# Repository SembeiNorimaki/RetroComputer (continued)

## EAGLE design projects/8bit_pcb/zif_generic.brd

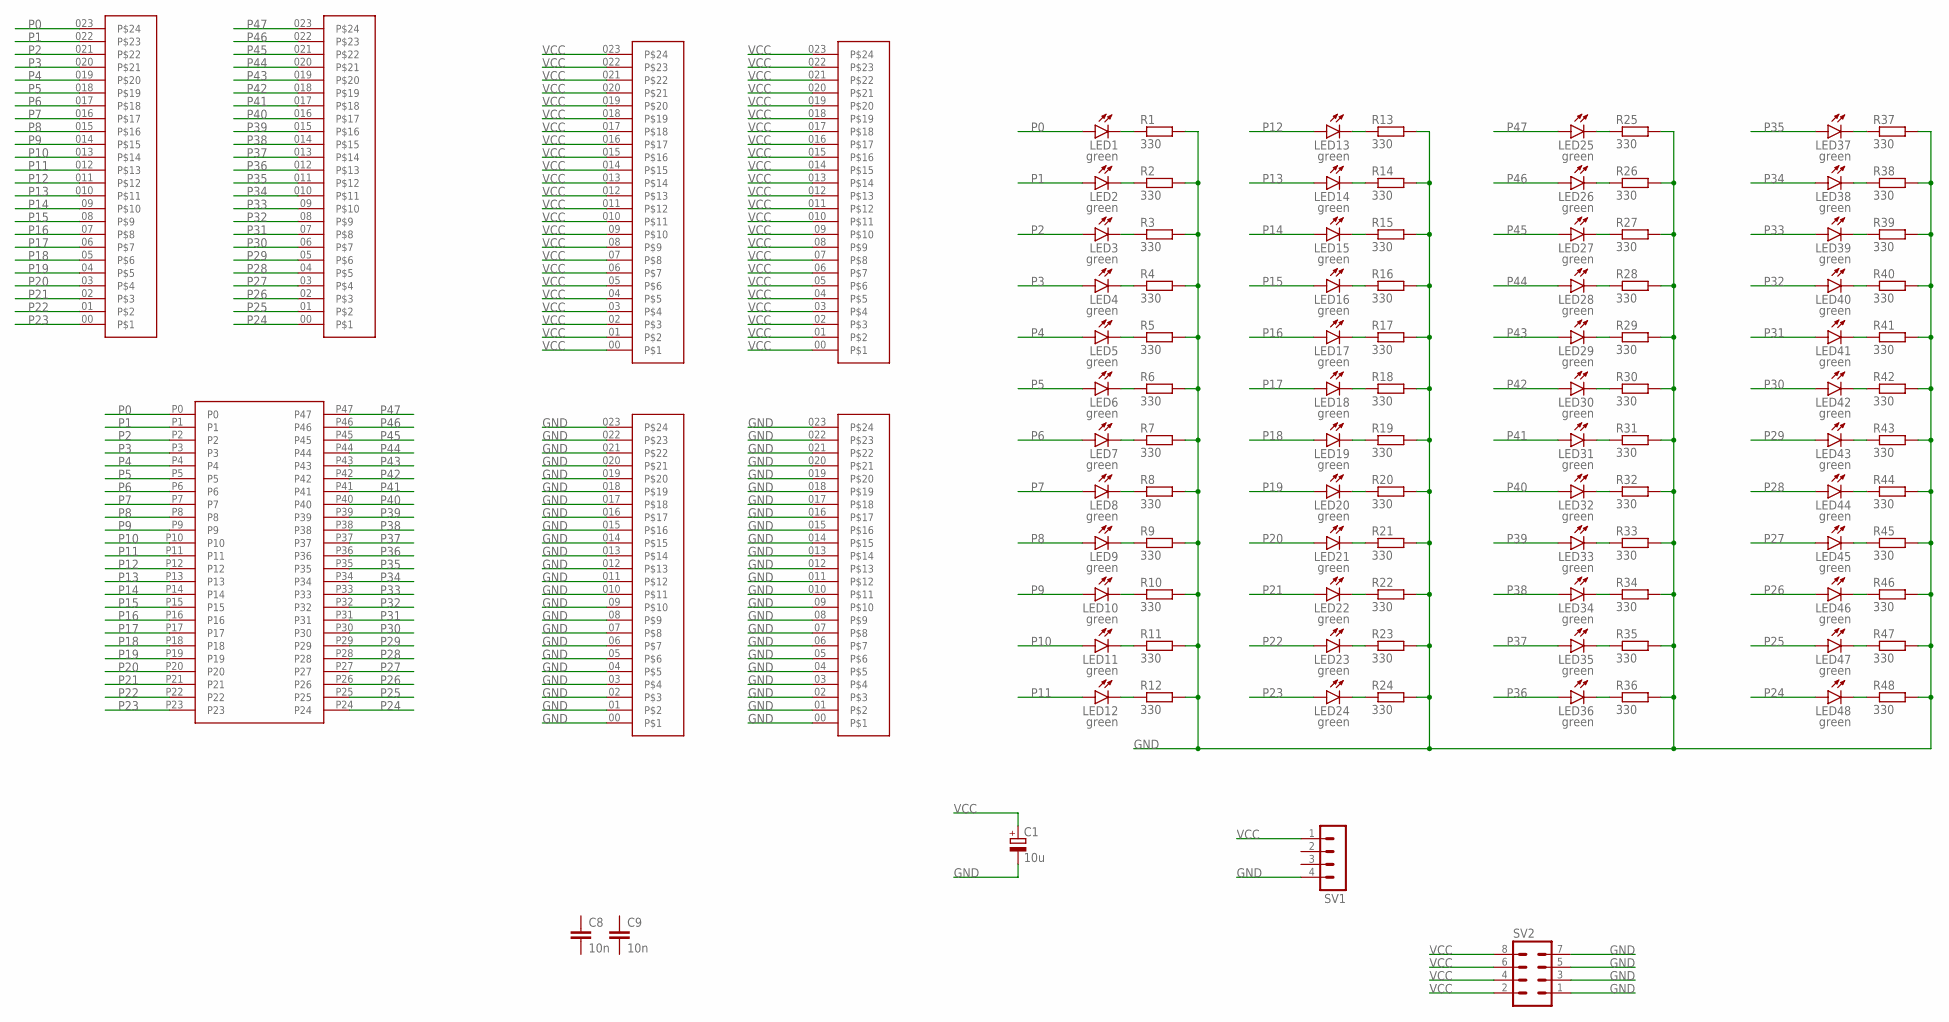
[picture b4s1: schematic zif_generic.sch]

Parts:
C1: 10u; E5-8,5
C8, C9: 10n; C050-025X075
LED1, LED2, LED3, LED4, LED5, LED6, LED7, LED8, LED9, LED10, LED11, LED12, LED13, LED14, LED15, LED16, LED17, LED18, LED19, LED20, LED21, LED22, LED23, LED24, LED25, LED26, LED27, LED28, LED29, LED30, LED31, LED32, LED33, LED34, LED35, LED36, LED37, LED38, LED39, LED40, LED41, LED42, LED43, LED44, LED45, LED46, LED47, LED48: green; SML1206
R1, R2, R3, R4, R5, R6, R7, R8, R9, R10, R11, R12, R13, R14, R15, R16, R17, R18, R19, R20, R21, R22, R23, R24, R25, R26, R27, R28, R29, R30, R31, R32, R33, R34, R35, R36, R37, R38, R39, R40, R41, R42, R43, R44, R45, R46, R47, R48: 330; R0805
SV1: MA04-1
SV2: MA04-2
U$1, U$2, U$3, U$4, U$5, U$6: PIN_1X24
U$7: ZIF_24X2

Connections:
GND: C1.-, R1.2, R2.2, R3.2, R4.2, R5.2, R6.2, R7.2, R8.2, R9.2, R10.2, R11.2, R12.2, R13.2, R14.2, R15.2, R16.2, R17.2, R18.2, R19.2, R20.2, R21.2, R22.2, R23.2, R24.2, R25.2, R26.2, R27.2, R28.2, R29.2, R30.2, R31.2, R32.2, R33.2, R34.2, R35.2, R36.2, R37.2, R38.2, R39.2, R40.2, R41.2, R42.2, R43.2, R44.2, R45.2, R46.2, R47.2, R48.2, SV1.4, SV2.1, SV2.3, SV2.5, SV2.7, U$2.00, U$2.01, U$2.02, U$2.03, U$2.04, U$2.05, U$2.06, U$2.07, U$2.08, U$2.09, U$2.010, U$2.011, U$2.012, U$2.013, U$2.014, U$2.015, U$2.016, U$2.017, U$2.018, U$2.019, U$2.020, U$2.021, U$2.022, U$2.023, U$5.00, U$5.01, U$5.02, U$5.03, U$5.04, U$5.05, U$5.06, U$5.07, U$5.08, U$5.09, U$5.010, U$5.011, U$5.012, U$5.013, U$5.014, U$5.015, U$5.016, U$5.017, U$5.018, U$5.019, U$5.020, U$5.021, U$5.022, U$5.023
unnamed: LED1.C, R1.1
unnamed: LED2.C, R2.1
unnamed: LED3.C, R3.1
unnamed: LED4.C, R4.1
unnamed: LED5.C, R5.1
unnamed: LED6.C, R6.1
unnamed: LED7.C, R7.1
unnamed: LED8.C, R8.1
unnamed: LED9.C, R9.1
unnamed: LED10.C, R10.1
unnamed: LED11.C, R11.1
unnamed: LED12.C, R12.1
unnamed: LED13.C, R13.1
unnamed: LED14.C, R14.1
unnamed: LED15.C, R15.1
unnamed: LED16.C, R16.1
unnamed: LED17.C, R17.1
unnamed: LED18.C, R18.1
unnamed: LED19.C, R19.1
unnamed: LED20.C, R20.1
unnamed: LED21.C, R21.1
unnamed: LED22.C, R22.1
unnamed: LED23.C, R23.1
unnamed: LED24.C, R24.1
unnamed: LED25.C, R25.1
unnamed: LED26.C, R26.1
unnamed: LED27.C, R27.1
unnamed: LED28.C, R28.1
unnamed: LED29.C, R29.1
unnamed: LED30.C, R30.1
unnamed: LED31.C, R31.1
unnamed: LED32.C, R32.1
unnamed: LED33.C, R33.1
unnamed: LED34.C, R34.1
unnamed: LED35.C, R35.1
unnamed: LED36.C, R36.1
unnamed: LED37.C, R37.1
unnamed: LED38.C, R38.1
unnamed: LED39.C, R39.1
unnamed: LED40.C, R40.1
unnamed: LED41.C, R41.1
unnamed: LED42.C, R42.1
unnamed: LED43.C, R43.1
unnamed: LED44.C, R44.1
unnamed: LED45.C, R45.1
unnamed: LED46.C, R46.1
unnamed: LED47.C, R47.1
unnamed: LED48.C, R48.1
P0: LED1.A, U$4.023, U$7.P0
P1: LED2.A, U$4.022, U$7.P1
P2: LED3.A, U$4.021, U$7.P2
P3: LED4.A, U$4.020, U$7.P3
P4: LED5.A, U$4.019, U$7.P4
P5: LED6.A, U$4.018, U$7.P5
P6: LED7.A, U$4.017, U$7.P6
P7: LED8.A, U$4.016, U$7.P7
P8: LED9.A, U$4.015, U$7.P8
P9: LED10.A, U$4.014, U$7.P9
P10: LED11.A, U$4.013, U$7.P10
P11: LED12.A, U$4.012, U$7.P11
P12: LED13.A, U$4.011, U$7.P12
P13: LED14.A, U$4.010, U$7.P13
P14: LED15.A, U$4.09, U$7.P14
P15: LED16.A, U$4.08, U$7.P15
P16: LED17.A, U$4.07, U$7.P16
P17: LED18.A, U$4.06, U$7.P17
P18: LED19.A, U$4.05, U$7.P18
P19: LED20.A, U$4.04, U$7.P19
P20: LED21.A, U$4.03, U$7.P20
P21: LED22.A, U$4.02, U$7.P21
P22: LED23.A, U$4.01, U$7.P22
P23: LED24.A, U$4.00, U$7.P23
P24: LED48.A, U$1.00, U$7.P24
P25: LED47.A, U$1.01, U$7.P25
P26: LED46.A, U$1.02, U$7.P26
P27: LED45.A, U$1.03, U$7.P27
P28: LED44.A, U$1.04, U$7.P28
P29: LED43.A, U$1.05, U$7.P29
P30: LED42.A, U$1.06, U$7.P30
P31: LED41.A, U$1.07, U$7.P31
P32: LED40.A, U$1.08, U$7.P32
P33: LED39.A, U$1.09, U$7.P33
P34: LED38.A, U$1.010, U$7.P34
P35: LED37.A, U$1.011, U$7.P35
P36: LED36.A, U$1.012, U$7.P36
P37: LED35.A, U$1.013, U$7.P37
P38: LED34.A, U$1.014, U$7.P38
P39: LED33.A, U$1.015, U$7.P39
P40: LED32.A, U$1.016, U$7.P40
P41: LED31.A, U$1.017, U$7.P41
P42: LED30.A, U$1.018, U$7.P42
P43: LED29.A, U$1.019, U$7.P43
P44: LED28.A, U$1.020, U$7.P44
P45: LED27.A, U$1.021, U$7.P45
P46: LED26.A, U$1.022, U$7.P46
P47: LED25.A, U$1.023, U$7.P47
VCC: C1.+, SV1.1, SV2.2, SV2.4, SV2.6, SV2.8, U$3.00, U$3.01, U$3.02, U$3.03, U$3.04, U$3.05, U$3.06, U$3.07, U$3.08, U$3.09, U$3.010, U$3.011, U$3.012, U$3.013, U$3.014, U$3.015, U$3.016, U$3.017, U$3.018, U$3.019, U$3.020, U$3.021, U$3.022, U$3.023, U$6.00, U$6.01, U$6.02, U$6.03, U$6.04, U$6.05, U$6.06, U$6.07, U$6.08, U$6.09, U$6.010, U$6.011, U$6.012, U$6.013, U$6.014, U$6.015, U$6.016, U$6.017, U$6.018, U$6.019, U$6.020, U$6.021, U$6.022, U$6.023

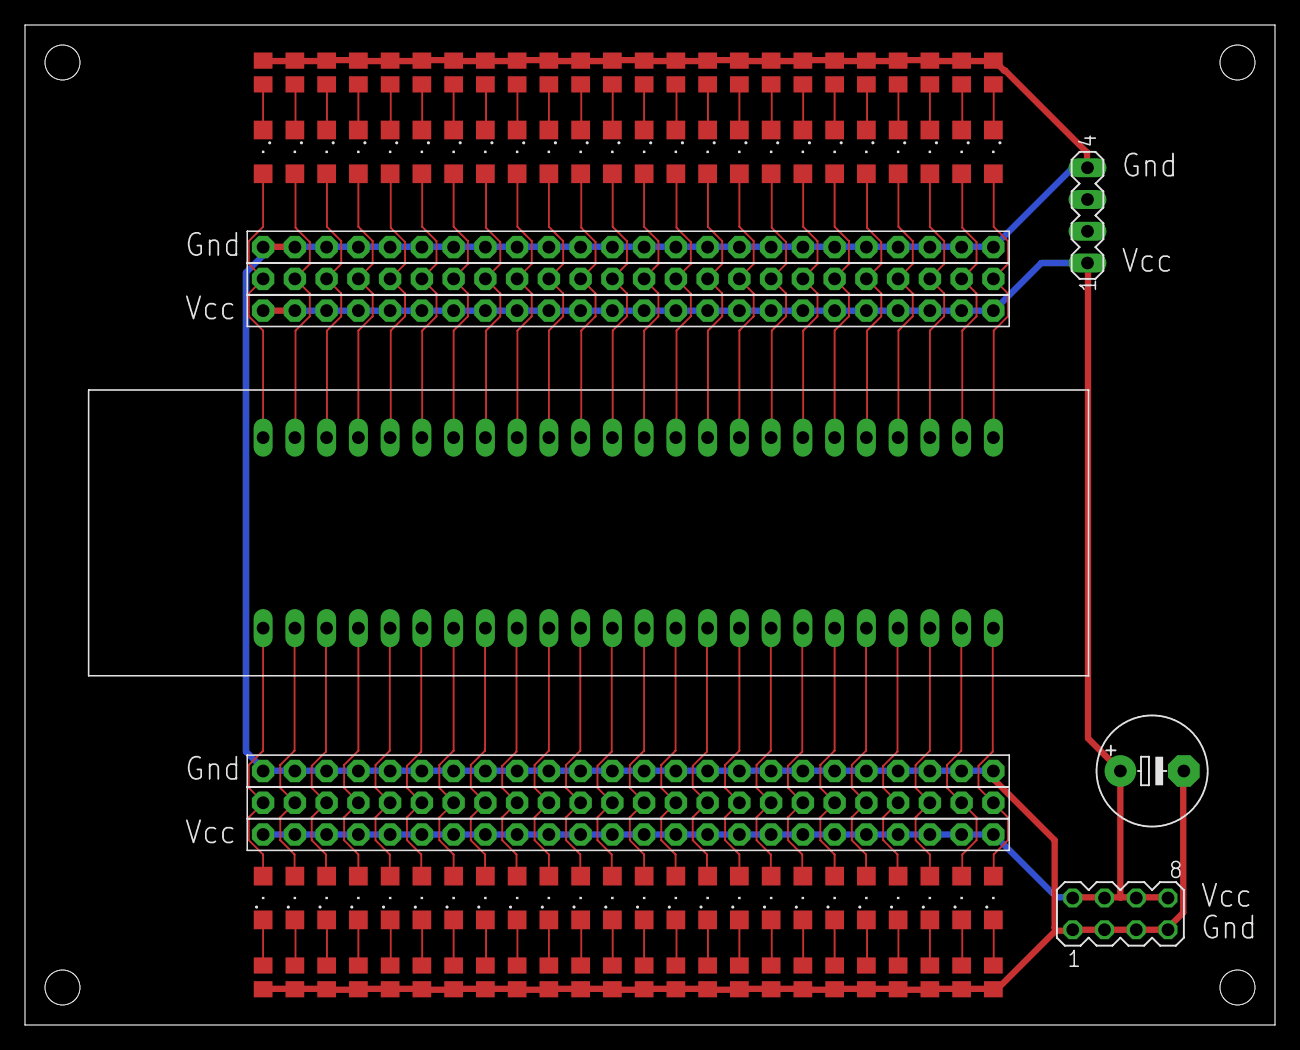
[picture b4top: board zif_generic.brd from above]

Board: 2 copper layers, 100.0 x 80.0 mm, 106 parts (0 on the bottom side), 98 nets.

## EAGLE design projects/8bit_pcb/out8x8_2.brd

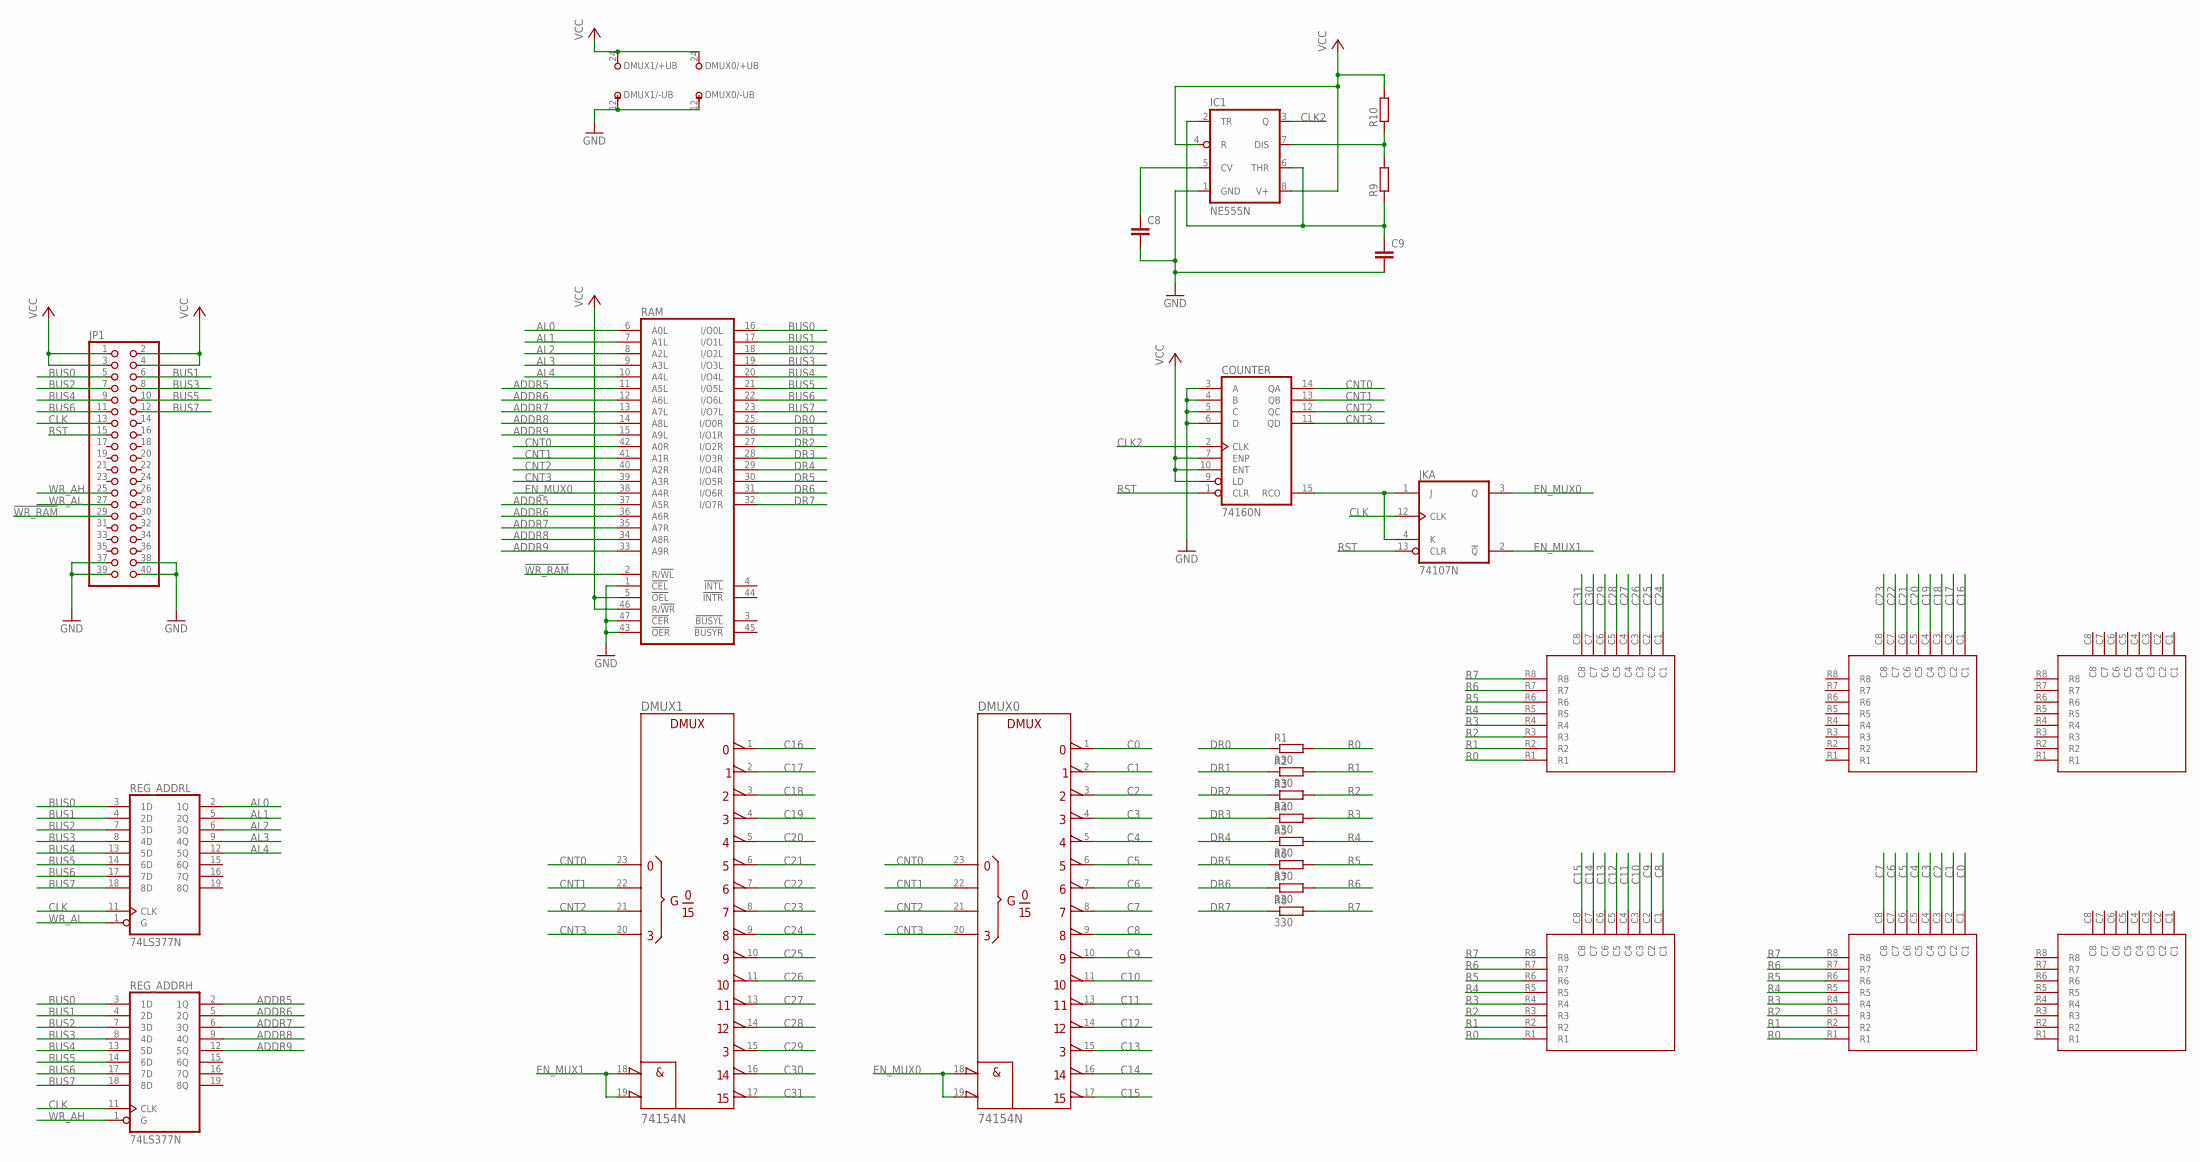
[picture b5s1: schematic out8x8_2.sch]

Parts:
C8, C9: C-EUC1206K; C1206K
COUNTER: 74160N; DIL16
DMUX0, DMUX1: 74154N; DIL24-3
IC1: NE555N; DIL08
JK: 74107N; DIL14
JP1: PINHD-2X20/90; 2X20/90
R1, R2, R3, R4, R5, R6, R7, R8: 330; R0805
R9, R10: R-EU_M1206; M1206
RAM: 7130P; DIL48
REG_ADDRH: 74LS377N; DIL20
REG_ADDRL: 74LS377N; DIL20
U$1, U$2, U$3, U$4, U$5, U$6: LED8X8

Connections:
!WR_RAM: JP1.29, RAM.2 (R/!WL)
ADDR5: RAM.11 (A5L), RAM.37 (A5R), REG_ADDRH.2 (1Q)
ADDR6: RAM.12 (A6L), RAM.36 (A6R), REG_ADDRH.5 (2Q)
ADDR7: RAM.13 (A7L), RAM.35 (A7R), REG_ADDRH.6 (3Q)
ADDR8: RAM.14 (A8L), RAM.34 (A8R), REG_ADDRH.9 (4Q)
ADDR9: RAM.15 (A9L), RAM.33 (A9R), REG_ADDRH.12 (5Q)
AL0: RAM.6 (A0L), REG_ADDRL.2 (1Q)
AL1: RAM.7 (A1L), REG_ADDRL.5 (2Q)
AL2: RAM.8 (A2L), REG_ADDRL.6 (3Q)
AL3: RAM.9 (A3L), REG_ADDRL.9 (4Q)
AL4: RAM.10 (A4L), REG_ADDRL.12 (5Q)
BUS0: JP1.5, RAM.16 (I/O0L), REG_ADDRH.3 (1D), REG_ADDRL.3 (1D)
BUS1: JP1.6, RAM.17 (I/O1L), REG_ADDRH.4 (2D), REG_ADDRL.4 (2D)
BUS2: JP1.7, RAM.18 (I/O2L), REG_ADDRH.7 (3D), REG_ADDRL.7 (3D)
BUS3: JP1.8, RAM.19 (I/O3L), REG_ADDRH.8 (4D), REG_ADDRL.8 (4D)
BUS4: JP1.9, RAM.20 (I/O4L), REG_ADDRH.13 (5D), REG_ADDRL.13 (5D)
BUS5: JP1.10, RAM.21 (I/O5L), REG_ADDRH.14 (6D), REG_ADDRL.14 (6D)
BUS6: JP1.11, RAM.22 (I/O6L), REG_ADDRH.17 (7D), REG_ADDRL.17 (7D)
BUS7: JP1.12, RAM.23 (I/O7L), REG_ADDRH.18 (8D), REG_ADDRL.18 (8D)
C0: DMUX0.1 (0), U$4.C1
C1: DMUX0.2 (1), U$4.C2
C2: DMUX0.3 (2), U$4.C3
C3: DMUX0.4 (3), U$4.C4
C4: DMUX0.5 (4), U$4.C5
C5: DMUX0.6 (5), U$4.C6
C6: DMUX0.7 (6), U$4.C7
C7: DMUX0.8 (7), U$4.C8
C8: DMUX0.9 (8), U$3.C1
C9: DMUX0.10 (9), U$3.C2
C10: DMUX0.11 (10), U$3.C3
C11: DMUX0.13 (11), U$3.C4
C12: DMUX0.14 (12), U$3.C5
C13: DMUX0.15 (13), U$3.C6
C14: DMUX0.16 (14), U$3.C7
C15: DMUX0.17 (15), U$3.C8
C16: DMUX1.1 (0), U$1.C1
C17: DMUX1.2 (1), U$1.C2
C18: DMUX1.3 (2), U$1.C3
C19: DMUX1.4 (3), U$1.C4
C20: DMUX1.5 (4), U$1.C5
C21: DMUX1.6 (5), U$1.C6
C22: DMUX1.7 (6), U$1.C7
C23: DMUX1.8 (7), U$1.C8
C24: DMUX1.9 (8), U$2.C1
C25: DMUX1.10 (9), U$2.C2
C26: DMUX1.11 (10), U$2.C3
C27: DMUX1.13 (11), U$2.C4
C28: DMUX1.14 (12), U$2.C5
C29: DMUX1.15 (13), U$2.C6
C30: DMUX1.16 (14), U$2.C7
C31: DMUX1.17 (15), U$2.C8
CLK: JK.12 (CLK), JP1.13, REG_ADDRH.11 (CLK), REG_ADDRL.11 (CLK)
CLK2: COUNTER.2 (CLK), IC1.3 (Q)
CNT0: COUNTER.14 (QA), DMUX0.23 (A), DMUX1.23 (A), RAM.42 (A0R)
CNT1: COUNTER.13 (QB), DMUX0.22 (B), DMUX1.22 (B), RAM.41 (A1R)
CNT2: COUNTER.12 (QC), DMUX0.21 (C), DMUX1.21 (C), RAM.40 (A2R)
CNT3: COUNTER.11 (QD), DMUX0.20 (D), DMUX1.20 (D), RAM.39 (A3R)
DR0: R1.1, RAM.25 (I/O0R)
DR1: R2.1, RAM.26 (I/O1R)
DR2: R3.1, RAM.27 (I/O2R)
DR3: R4.1, RAM.28 (I/O3R)
DR4: R5.1, RAM.29 (I/O4R)
DR5: R6.1, RAM.30 (I/O5R)
DR6: R7.1, RAM.31 (I/O6R)
DR7: R8.1, RAM.32 (I/O7R)
EN_MUX0: DMUX0.18 (!G1), DMUX0.19 (!G2), JK.3 (Q), RAM.38 (A4R)
EN_MUX1: DMUX1.18 (!G1), DMUX1.19 (!G2), JK.2 (!Q)
GND: C8.2, C9.2, COUNTER.3 (A), COUNTER.4 (B), COUNTER.5 (C), COUNTER.6 (D), COUNTER.8 (GND), DMUX0.12 (-UB), DMUX1.12 (-UB), IC1.1 (GND), JK.7 (GND), JP1.37, JP1.38, JP1.39, JP1.40, RAM.1 (!CEL), RAM.24 (GND), RAM.43 (!OER), RAM.47 (!CER), REG_ADDRH.10 (GND), REG_ADDRL.10 (GND)
unnamed: COUNTER.15 (RCO), JK.1 (J), JK.4 (K)
unnamed: IC1.7 (DIS), R9.2, R10.1
unnamed: C8.1, IC1.5 (CV)
unnamed: C9.1, IC1.2 (TR), IC1.6 (THR), R9.1
R0: R1.2, U$2.R1, U$3.R1, U$4.R1
R1: R2.2, U$2.R2, U$3.R2, U$4.R2
R2: R3.2, U$2.R3, U$3.R3, U$4.R3
R3: R4.2, U$2.R4, U$3.R4, U$4.R4
R4: R5.2, U$2.R5, U$3.R5, U$4.R5
R5: R6.2, U$2.R6, U$3.R6, U$4.R6
R6: R7.2, U$2.R7, U$3.R7, U$4.R7
R7: R8.2, U$2.R8, U$3.R8, U$4.R8
RST: COUNTER.1 (CLR), JK.13 (CLR), JP1.15
VCC: COUNTER.7 (ENP), COUNTER.9 (LD), COUNTER.10 (ENT), COUNTER.16 (VCC), DMUX0.24 (+UB), DMUX1.24 (+UB), IC1.4 (R), IC1.8 (V+), JK.14 (VCC), JP1.1, JP1.2, JP1.3, JP1.4, R10.2, RAM.5 (!OEL), RAM.46 (R/!WR), RAM.48 (VCC), REG_ADDRH.20 (VCC), REG_ADDRL.20 (VCC)
WR_AH: JP1.25, REG_ADDRH.1 (G)
WR_AL: JP1.27, REG_ADDRL.1 (G)

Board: 2 copper layers, 27 parts (0 on the bottom side), 84 nets, no tracks yet.

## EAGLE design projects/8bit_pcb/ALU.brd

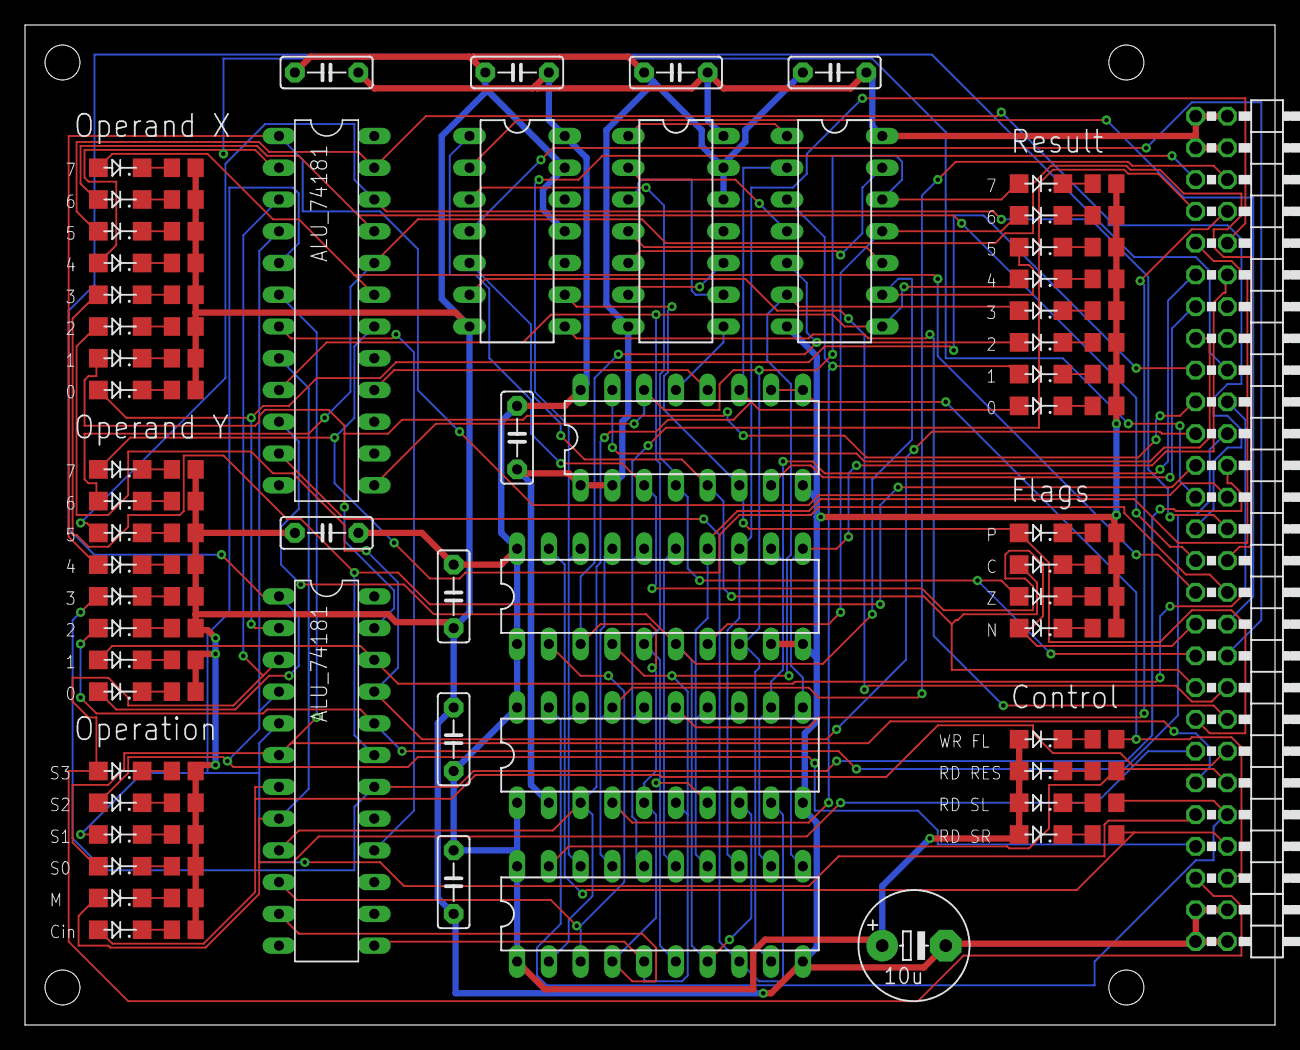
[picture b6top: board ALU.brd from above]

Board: 2 copper layers, 100.0 x 80.0 mm, 97 parts (0 on the bottom side), 101 nets.

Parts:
ALU0, ALU1: ALU_74181
AND: 74LS08N; DIL14
BUFF_R: 74LS245N; DIL20
BUFF_SL: 74LS245N; DIL20
BUFF_SR: 74LS245N; DIL20
C1: 10u; E5-8,5
C2, C3, C4, C5, C6, C7, C8, C9, C10: 10n; C5B2.5
JP1: 2X25/90
JP2: 2X02/90
LED1, LED2, LED3, LED4, LED5, LED6, LED7, LED8, LED9, LED10, LED11, LED12, LED13, LED14, LED15, LED16, LED17, LED18, LED19, LED20, LED21, LED22, LED23, LED24: green; SML1206
LED25, LED26, LED27, LED28, LED29, LED30, LED31, LED32, LED33, LED36: yellow; SML1206
LED34, LED35, LED37, LED38: red; SML1206
NOR: 74LS02N; DIL14
NOT: 74LS04N; DIL14
R1, R2, R3, R4, R5, R6, R7, R8, R9, R10, R11, R12, R13, R14, R15, R16, R17, R18, R19, R20, R21, R22, R23, R24, R25, R26, R27, R28, R29, R30, R31, R32, R33, R34, R35, R36, R37, R38: 330; R0805
REG_FLAGS: 74LS173N; DIL16

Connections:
!RD_ALU: BUFF_R.19, JP1.44, R35.2
!RD_SL: BUFF_SL.19, JP1.46, R37.2
!RD_SR: BUFF_SR.19, JP1.48, R38.2
!WR_FL: JP1.50, R34.2, REG_FLAGS.9, REG_FLAGS.10
A0: ALU0.A0, JP1.17, LED1.A
A1: ALU0.A1, JP1.19, LED2.A
A2: ALU0.A2, JP1.21, LED3.A
A3: ALU0.A3, JP1.23, LED4.A
A4: ALU1.A0, JP1.25, LED5.A
A5: ALU1.A1, JP1.27, LED6.A
A6: ALU1.A2, JP1.29, LED7.A
A7: ALU1.A3, JP1.31, LED8.A
B0: ALU0.B0, JP1.18, LED9.A
B1: ALU0.B1, JP1.20, LED10.A
B2: ALU0.B2, JP1.22, LED11.A
B3: ALU0.B3, JP1.24, LED12.A
B4: ALU1.B0, JP1.26, LED13.A
B5: ALU1.B1, JP1.28, LED14.A
B6: ALU1.B2, JP1.30, LED15.A
B7: ALU1.B3, JP1.32, LED16.A
BUS0: BUFF_R.18, BUFF_SL.18, BUFF_SR.18, JP1.5
BUS1: BUFF_R.17, BUFF_SL.17, BUFF_SR.17, JP1.6
BUS2: BUFF_R.16, BUFF_SL.16, BUFF_SR.16, JP1.7
BUS3: BUFF_R.15, BUFF_SL.15, BUFF_SR.15, JP1.8
BUS4: BUFF_R.14, BUFF_SL.14, BUFF_SR.14, JP1.9
BUS5: BUFF_R.13, BUFF_SL.13, BUFF_SR.13, JP1.10
BUS6: BUFF_R.12, BUFF_SL.12, BUFF_SR.12, JP1.11
BUS7: BUFF_R.11, BUFF_SL.11, BUFF_SR.11, JP1.12
CIN: ALU0.CN, JP1.42, LED36.A
CLK: JP1.13, REG_FLAGS.7
CLR_FL: JP1.15, REG_FLAGS.15
C_OUT: ALU1.COUT, REG_FLAGS.12
FL_C: JP1.37, LED27.A, NOT.5, REG_FLAGS.5
FL_N: JP1.33, LED25.A, NOT.1, REG_FLAGS.3
FL_P: JP1.39, LED28.A, NOT.9, REG_FLAGS.6
FL_Z: JP1.35, LED26.A, NOT.3, REG_FLAGS.4
GND: AND.7, AND.12, AND.13, BUFF_R.10, BUFF_SL.2, BUFF_SL.10, BUFF_SR.9, BUFF_SR.10, C1.-, C2.2, C3.2, C4.2, C5.2, C6.2, C7.2, C8.2, C9.2, C10.2, JP2.1, JP2.2, JP2.3, JP2.4, NOR.7, NOT.7, NOT.11, NOT.13, R1.2, R2.2, R3.2, R4.2, R5.2, R6.2, R7.2, R8.2, R9.2, R10.2, R11.2, R12.2, R13.2, R14.2, R15.2, R16.2, R17.2, R18.2, R19.2, R20.2, R21.2, R22.2, R23.2, R24.2, R25.2, R26.2, R27.2, R28.2, R29.2, R30.2, R31.2, R32.2, R33.2, R36.2, REG_FLAGS.1, REG_FLAGS.2, REG_FLAGS.8
IFL_C: JP1.38, NOT.6
IFL_N: JP1.34, NOT.2
IFL_P: JP1.40, NOT.8
IFL_Z: JP1.36, NOT.4
M: ALU0.M, ALU1.M, JP1.41, LED33.A
unnamed: ALU0.COUT, ALU1.CN
unnamed: AND.1, NOR.1
unnamed: AND.2, NOR.4
unnamed: AND.4, NOR.10
unnamed: AND.5, NOR.13
unnamed: AND.6, AND.10
unnamed: AND.3, AND.9
unnamed: LED29.C, R29.1
unnamed: LED1.C, R1.1
unnamed: LED2.C, R2.1
unnamed: LED3.C, R3.1
unnamed: LED4.C, R4.1
unnamed: LED5.C, R5.1
unnamed: LED6.C, R6.1
unnamed: LED7.C, R7.1
unnamed: LED8.C, R8.1
unnamed: LED30.C, R30.1
unnamed: LED9.C, R9.1
unnamed: LED10.C, R10.1
unnamed: LED11.C, R11.1
unnamed: LED12.C, R12.1
unnamed: LED13.C, R13.1
unnamed: LED14.C, R14.1
unnamed: LED15.C, R15.1
unnamed: LED16.C, R16.1
unnamed: LED31.C, R31.1
unnamed: LED17.C, R17.1
unnamed: LED18.C, R18.1
unnamed: LED19.C, R19.1
unnamed: LED20.C, R20.1
unnamed: LED21.C, R21.1
unnamed: LED22.C, R22.1
unnamed: LED23.C, R23.1
unnamed: LED24.C, R24.1
unnamed: LED25.C, R25.1
unnamed: LED26.C, R26.1
unnamed: LED27.C, R27.1
unnamed: LED28.C, R28.1
unnamed: LED32.C, R32.1
unnamed: LED33.C, R33.1
unnamed: LED34.C, R34.1
unnamed: LED35.C, R35.1
unnamed: LED36.C, R36.1
unnamed: LED37.C, R37.1
unnamed: LED38.C, R38.1
R0: ALU0.F0, BUFF_R.2, BUFF_SL.3, LED17.A, NOR.2, REG_FLAGS.11
R1: ALU0.F1, BUFF_R.3, BUFF_SL.4, BUFF_SR.2, LED18.A, NOR.3
R2: ALU0.F2, BUFF_R.4, BUFF_SL.5, BUFF_SR.3, LED19.A, NOR.5
R3: ALU0.F3, BUFF_R.5, BUFF_SL.6, BUFF_SR.4, LED20.A, NOR.6
R4: ALU1.F0, BUFF_R.6, BUFF_SL.7, BUFF_SR.5, LED21.A, NOR.8
R5: ALU1.F1, BUFF_R.7, BUFF_SL.8, BUFF_SR.6, LED22.A, NOR.9
R6: ALU1.F2, BUFF_R.8, BUFF_SL.9, BUFF_SR.7, LED23.A, NOR.11
R7: ALU1.F3, BUFF_R.9, BUFF_SR.8, LED24.A, NOR.12, REG_FLAGS.14
S0: ALU0.S0, ALU1.S0, JP1.43, LED29.A
S1: ALU0.S1, ALU1.S1, JP1.45, LED30.A
S2: ALU0.S2, ALU1.S2, JP1.47, LED31.A
S3: ALU0.S3, ALU1.S3, JP1.49, LED32.A
VCC: AND.14, BUFF_R.1, BUFF_R.20, BUFF_SL.1, BUFF_SL.20, BUFF_SR.1, BUFF_SR.20, C1.+, C2.1, C3.1, C4.1, C5.1, C6.1, C7.1, C8.1, C9.1, C10.1, JP1.1, JP1.2, JP1.3, JP1.4, LED34.A, LED35.A, LED37.A, LED38.A, NOR.14, NOT.14, REG_FLAGS.16
Z: AND.8, REG_FLAGS.13

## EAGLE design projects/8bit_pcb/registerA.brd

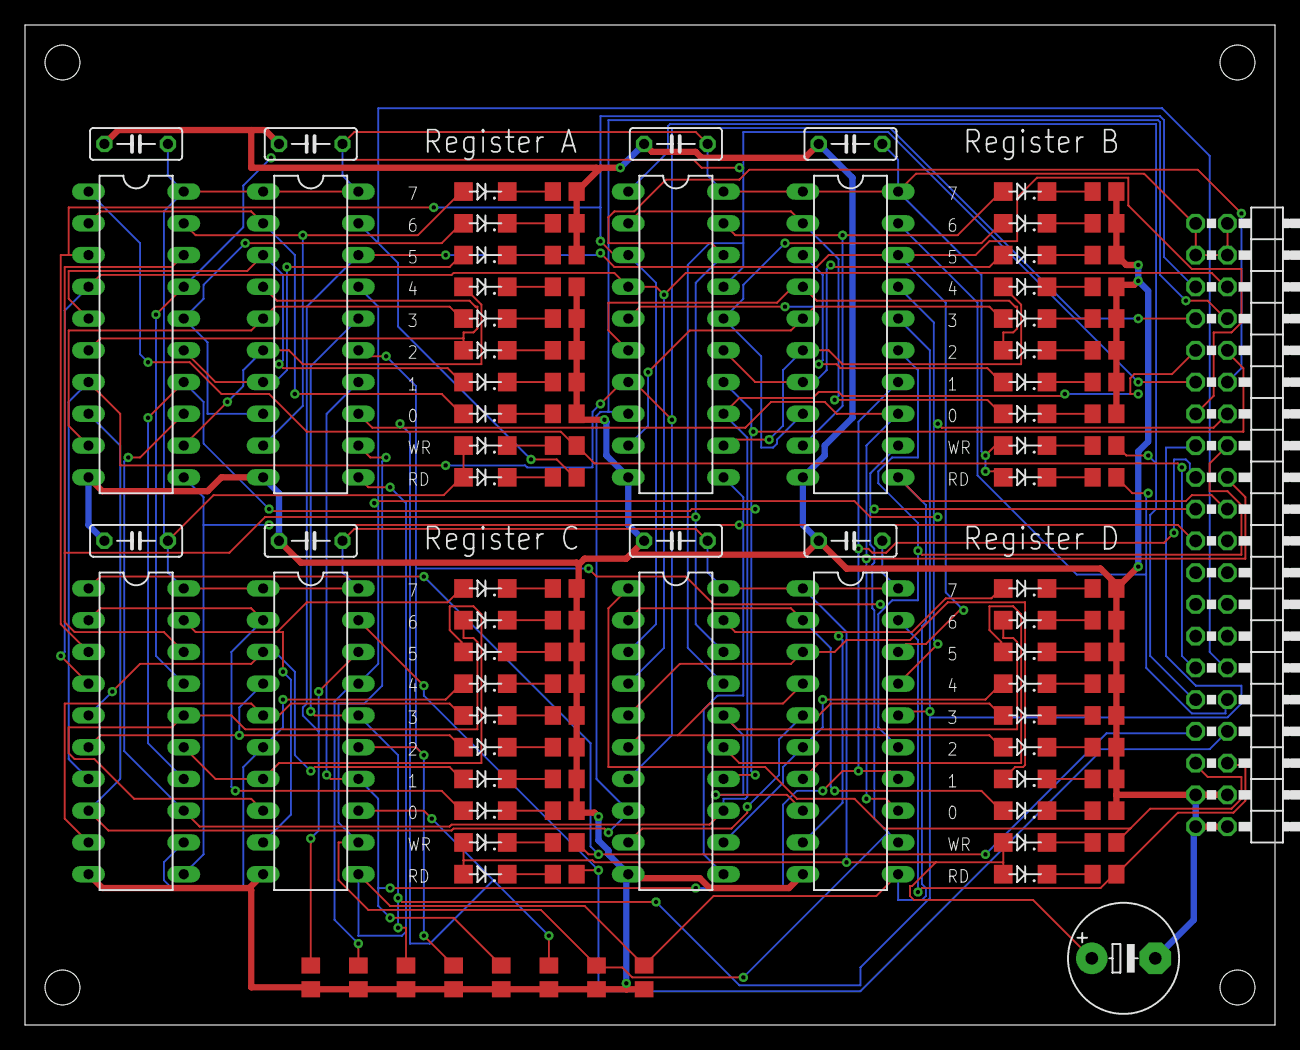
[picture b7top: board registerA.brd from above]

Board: 2 copper layers, 100.0 x 80.0 mm, 106 parts (0 on the bottom side), 99 nets.

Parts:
BUFF_A: 74LS245N; DIL20
BUFF_B: 74LS245N; DIL20
BUFF_C: 74LS245N; DIL20
BUFF_D: 74LS245N; DIL20
C1: 10u; E5-8,5
C2, C3, C4, C5, C6, C7, C8, C9: 10n; C050-025X075
JP1: 2X20/90
LED1, LED2, LED3, LED4, LED5, LED6, LED7, LED8, LED9, LED10, LED11, LED12, LED13, LED14, LED15, LED16, LED17, LED18, LED19, LED20, LED21, LED22, LED23, LED24, LED25, LED26, LED27, LED28, LED29, LED30, LED31, LED32: green; SML1206
R1, R2, R3, R4, R5, R6, R7, R8, R9, R10, R11, R12, R13, R14, R15, R16, R17, R18, R19, R20, R21, R22, R23, R24, R25, R26, R27, R28, R29, R30, R31, R32, R33, R34, R35, R36, R37, R38, R39, R40, R41, R42, R43, R44, R45, R46, R47, R48: 330; R0805
RD_A: red; SML1206
RD_B: red; SML1206
RD_C: red; SML1206
RD_D: red; SML1206
REG_A: 74LS377N; DIL20
REG_B: 74LS377N; DIL20
REG_C: 74LS377N; DIL20
REG_D: 74LS377N; DIL20
WR_A: red; SML1206
WR_B: red; SML1206
WR_C: red; SML1206
WR_D: red; SML1206

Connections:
!RDA: BUFF_A.19, JP1.30, R34.2
!RDB: BUFF_B.19, JP1.32, R36.2
!RDC: BUFF_C.19, JP1.34, R38.2
!RDD: BUFF_D.19, JP1.36, R40.2
!WRA: JP1.29, R33.2, REG_A.1
!WRB: JP1.31, R35.2, REG_B.1
!WRC: JP1.33, R37.2, REG_C.1
!WRD: JP1.35, R39.2, REG_D.1
A0: BUFF_A.2, LED1.A, REG_A.2
A1: BUFF_A.3, LED2.A, REG_A.5
A2: BUFF_A.4, LED3.A, REG_A.6
A3: BUFF_A.5, LED4.A, REG_A.9
A4: BUFF_A.6, LED5.A, REG_A.12
A5: BUFF_A.7, LED6.A, REG_A.15
A6: BUFF_A.8, LED7.A, REG_A.16
A7: BUFF_A.9, LED8.A, REG_A.19
B0: BUFF_B.2, LED9.A, REG_B.2
B1: BUFF_B.3, LED10.A, REG_B.5
B2: BUFF_B.4, LED11.A, REG_B.6
B3: BUFF_B.5, LED12.A, REG_B.9
B4: BUFF_B.6, LED13.A, REG_B.12
B5: BUFF_B.7, LED14.A, REG_B.15
B6: BUFF_B.8, LED15.A, REG_B.16
B7: BUFF_B.9, LED16.A, REG_B.19
BUS0: JP1.5, REG_A.3, REG_B.3, REG_C.3, REG_D.3
BUS1: JP1.6, REG_A.4, REG_B.4, REG_C.4, REG_D.4
BUS2: JP1.7, REG_A.7, REG_B.7, REG_C.7, REG_D.7
BUS3: JP1.8, REG_A.8, REG_B.8, REG_C.8, REG_D.8
BUS4: JP1.9, REG_A.13, REG_B.13, REG_C.13, REG_D.13
BUS5: JP1.10, REG_A.14, REG_B.14, REG_C.14, REG_D.14
BUS6: JP1.11, REG_A.17, REG_B.17, REG_C.17, REG_D.17
BUS7: JP1.12, REG_A.18, REG_B.18, REG_C.18, REG_D.18
C0: BUFF_C.2, LED17.A, REG_C.2
C1: BUFF_C.3, LED18.A, REG_C.5
C2: BUFF_C.4, LED19.A, REG_C.6
C3: BUFF_C.5, LED20.A, REG_C.9
C4: BUFF_C.6, LED21.A, REG_C.12
C5: BUFF_C.7, LED22.A, REG_C.15
C6: BUFF_C.8, LED23.A, REG_C.16
C7: BUFF_C.9, LED24.A, REG_C.19
CLK: JP1.21, REG_A.11, REG_B.11, REG_C.11, REG_D.11
D0: BUFF_D.2, LED25.A, REG_D.2
D1: BUFF_D.3, LED26.A, REG_D.5
D2: BUFF_D.4, LED27.A, REG_D.6
D3: BUFF_D.5, LED28.A, REG_D.9
D4: BUFF_D.6, LED29.A, REG_D.12
D5: BUFF_D.7, LED30.A, REG_D.15
D6: BUFF_D.8, LED31.A, REG_D.16
D7: BUFF_D.9, LED32.A, REG_D.19
GND: BUFF_A.10, BUFF_B.10, BUFF_C.10, BUFF_D.10, C1.-, C2.2, C3.2, C4.2, C5.2, C6.2, C7.2, C8.2, C9.2, JP1.37, JP1.38, JP1.39, JP1.40, R1.2, R2.2, R3.2, R4.2, R5.2, R6.2, R7.2, R8.2, R9.2, R10.2, R11.2, R12.2, R13.2, R14.2, R15.2, R16.2, R17.2, R18.2, R19.2, R20.2, R21.2, R22.2, R23.2, R24.2, R25.2, R26.2, R27.2, R28.2, R29.2, R30.2, R31.2, R32.2, R41.2, R42.2, R43.2, R44.2, R45.2, R46.2, R47.2, R48.2, REG_A.10, REG_B.10, REG_C.10, REG_D.10
unnamed: LED1.C, R1.1
unnamed: LED2.C, R2.1
unnamed: LED3.C, R3.1
unnamed: LED4.C, R4.1
unnamed: LED5.C, R5.1
unnamed: LED6.C, R6.1
unnamed: LED7.C, R7.1
unnamed: LED8.C, R8.1
unnamed: LED9.C, R9.1
unnamed: LED10.C, R10.1
unnamed: LED11.C, R11.1
unnamed: LED12.C, R12.1
unnamed: LED13.C, R13.1
unnamed: LED14.C, R14.1
unnamed: LED15.C, R15.1
unnamed: LED16.C, R16.1
unnamed: LED17.C, R17.1
unnamed: LED18.C, R18.1
unnamed: LED19.C, R19.1
unnamed: LED20.C, R20.1
unnamed: LED21.C, R21.1
unnamed: LED22.C, R22.1
unnamed: LED23.C, R23.1
unnamed: LED24.C, R24.1
unnamed: LED25.C, R25.1
unnamed: LED26.C, R26.1
unnamed: LED27.C, R27.1
unnamed: LED28.C, R28.1
unnamed: LED29.C, R29.1
unnamed: LED30.C, R30.1
unnamed: LED31.C, R31.1
unnamed: LED32.C, R32.1
unnamed: R33.1, WR_A.C
unnamed: R34.1, RD_A.C
unnamed: R35.1, WR_B.C
unnamed: R36.1, RD_B.C
unnamed: R37.1, WR_C.C
unnamed: R38.1, RD_C.C
unnamed: R39.1, WR_D.C
unnamed: R40.1, RD_D.C
VCC: BUFF_A.1, BUFF_A.20, BUFF_B.1, BUFF_B.20, BUFF_C.1, BUFF_C.20, BUFF_D.1, BUFF_D.20, C1.+, C2.1, C3.1, C4.1, C5.1, C6.1, C7.1, C8.1, C9.1, JP1.1, JP1.2, JP1.3, JP1.4, RD_A.A, RD_B.A, RD_C.A, RD_D.A, REG_A.20, REG_B.20, REG_C.20, REG_D.20, WR_A.A, WR_B.A, WR_C.A, WR_D.A
X0: BUFF_A.18, BUFF_B.18, BUFF_C.18, BUFF_D.18, JP1.13, R41.1
X1: BUFF_A.17, BUFF_B.17, BUFF_C.17, BUFF_D.17, JP1.14, R42.1
X2: BUFF_A.16, BUFF_B.16, BUFF_C.16, BUFF_D.16, JP1.15, R43.1
X3: BUFF_A.15, BUFF_B.15, BUFF_C.15, BUFF_D.15, JP1.16, R44.1
X4: BUFF_A.14, BUFF_B.14, BUFF_C.14, BUFF_D.14, JP1.17, R45.1
X5: BUFF_A.13, BUFF_B.13, BUFF_C.13, BUFF_D.13, JP1.18, R46.1
X6: BUFF_A.12, BUFF_B.12, BUFF_C.12, BUFF_D.12, JP1.19, R47.1
X7: BUFF_A.11, BUFF_B.11, BUFF_C.11, BUFF_D.11, JP1.20, R48.1

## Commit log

2023-12-27 RAM, Disp16Seg, Decoder
